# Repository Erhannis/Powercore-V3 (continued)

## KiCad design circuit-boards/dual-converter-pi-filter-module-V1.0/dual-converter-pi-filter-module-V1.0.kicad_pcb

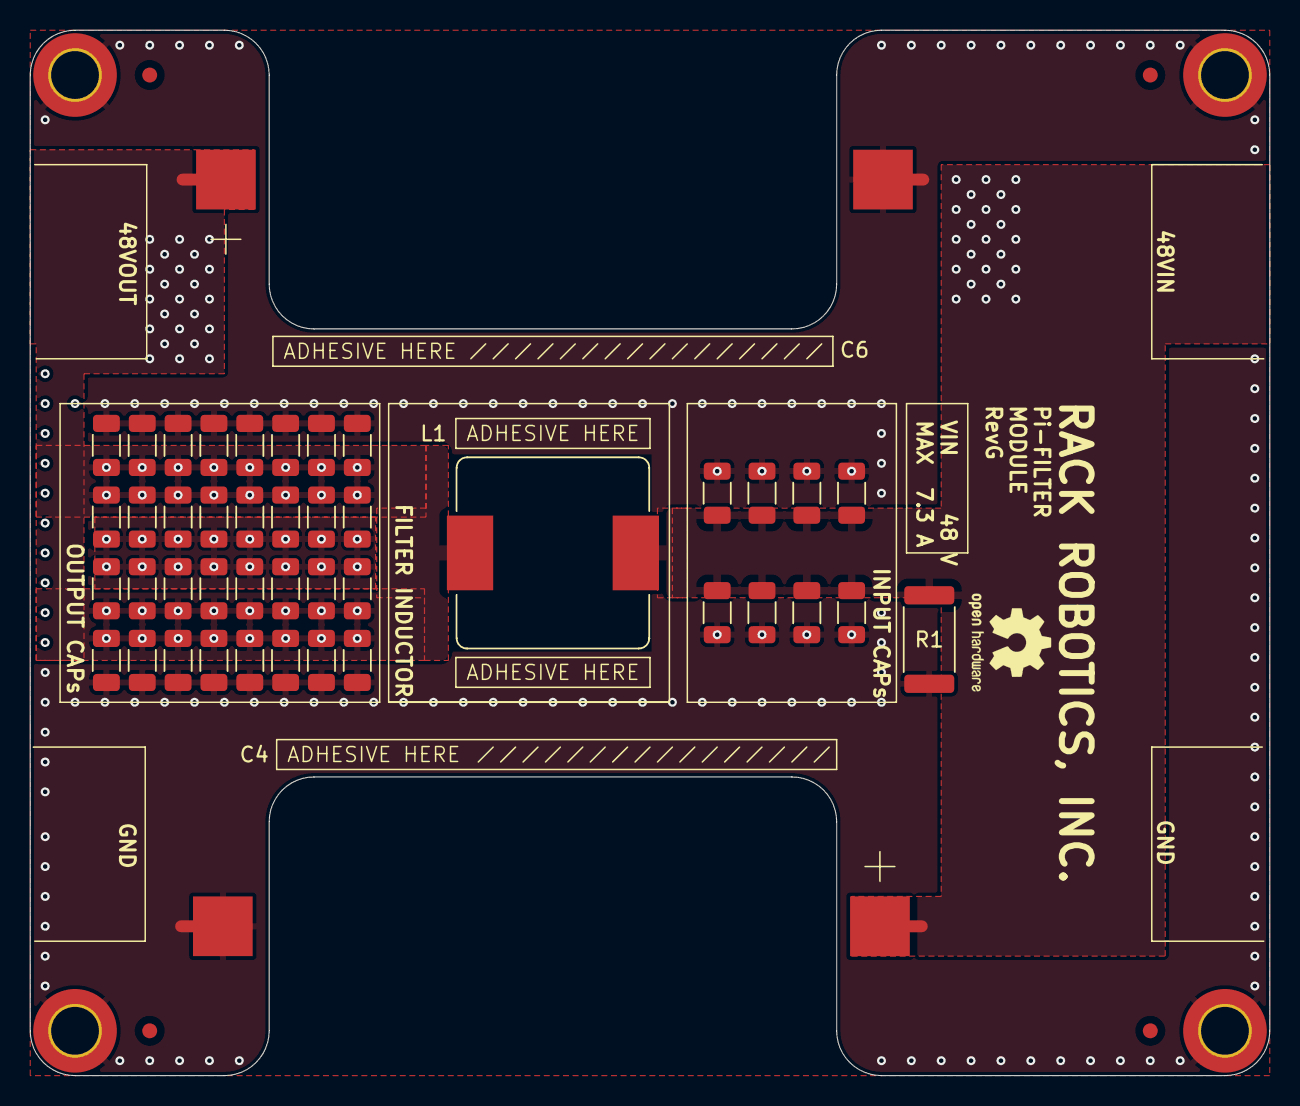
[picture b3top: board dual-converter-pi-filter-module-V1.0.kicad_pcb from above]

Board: 4 copper layers, 83.0 x 70.0 mm, 48 parts (0 on the bottom side), 3 nets.

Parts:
C1, C2, C3, C5, C7, C8, C9, C10, C11, C12, C13, C14, C15, C16, C17, C18, C19, C20, C21, C22, C23, C24, C25, C26, C27, C28, C29, C30, C31, C32, C33, C34, C35, C36, C37, C38, C39, C40, C41, C42: 10 uF; C_1206_3216Metric
C4, C6: 560 uF; PHA225
H1, H2, H3, H4: M3_DIN; MountingHole_3.2mm_M3_DIN965_Pad_TopBottom
L1: 18uH; SRP1245A
R1: 4.7K; R_2512_6332Metric

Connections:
+48V: C1.1, C2.1, C3.1, C4.1, C5.1, C7.1, C8.1, C9.1, C10.1, L1.1, R1.2
/FILTER_OUT: C6.1, C11.1, C12.1, C13.1, C14.1, C15.1, C16.1, C17.1, C18.1, C19.1, C20.1, C21.1, C22.1, C23.1, C24.1, C25.1, C26.1, C27.1, C28.1, C29.1, C30.1, C31.1, C32.1, C33.1, C34.1, C35.1, C36.1, C37.1, C38.1, C39.1, C40.1, C41.1, C42.1, L1.2
GND: C1.2, C2.2, C3.2, C4.2, C5.2, C6.2, C7.2, C8.2, C9.2, C10.2, C11.2, C12.2, C13.2, C14.2, C15.2, C16.2, C17.2, C18.2, C19.2, C20.2, C21.2, C22.2, C23.2, C24.2, C25.2, C26.2, C27.2, C28.2, C29.2, C30.2, C31.2, C32.2, C33.2, C34.2, C35.2, C36.2, C37.2, C38.2, C39.2, C40.2, C41.2, C42.2, H1.1, H2.1, H3.1, H4.1, R1.1

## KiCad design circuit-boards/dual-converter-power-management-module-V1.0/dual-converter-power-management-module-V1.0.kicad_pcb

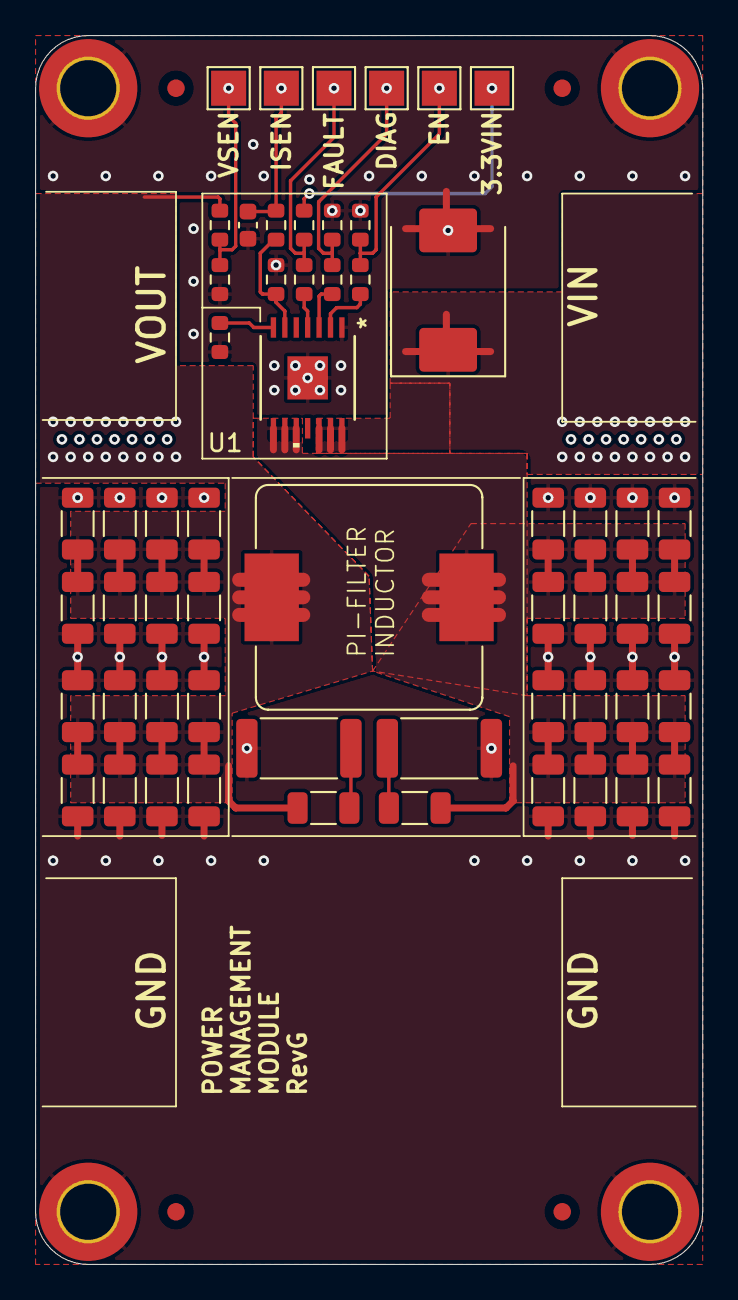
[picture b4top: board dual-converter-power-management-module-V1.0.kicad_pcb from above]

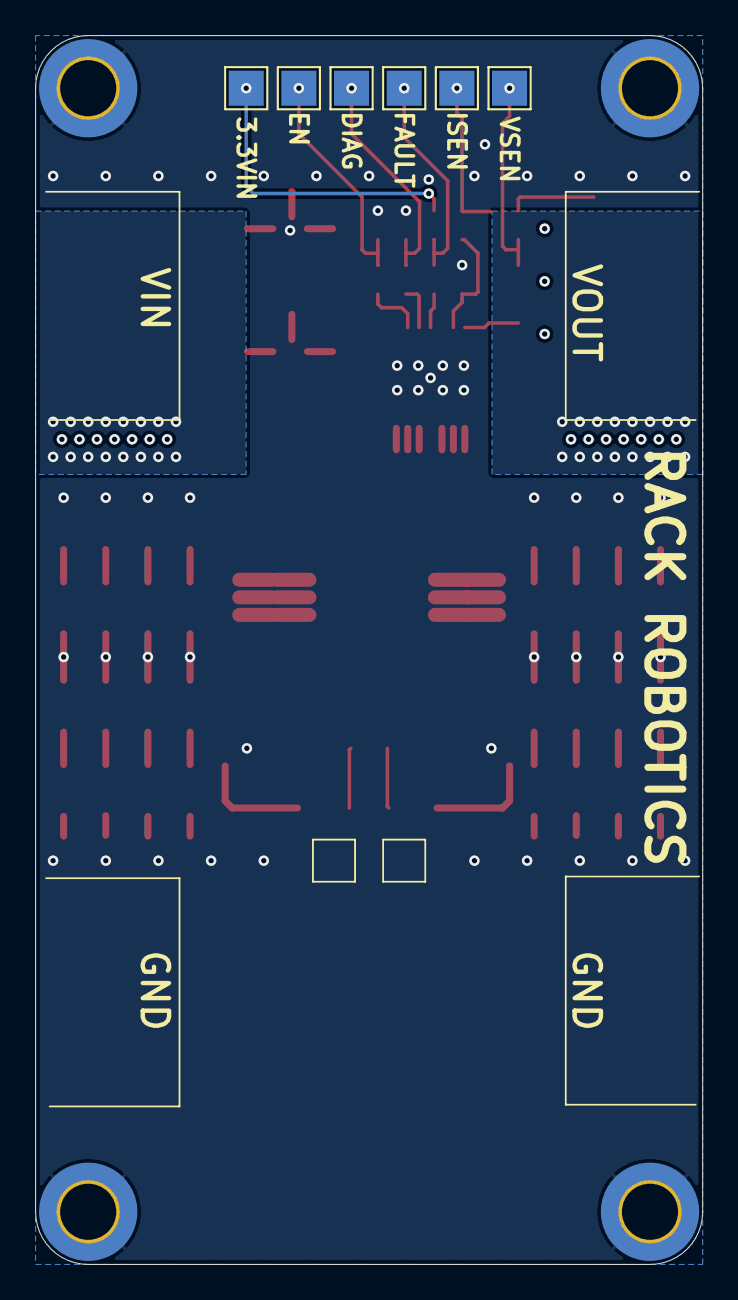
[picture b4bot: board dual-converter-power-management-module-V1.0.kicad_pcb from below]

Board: 4 copper layers, 38.0 x 70.0 mm, 67 parts (6 on the bottom side), 17 nets.

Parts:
C1: 1 uF; C_0603_1608Metric
C2, C3, C4, C5, C6, C7, C8, C9, C10, C11, C12, C13, C14, C15, C16, C17, C18, C19, C20, C21, C22, C23, C24, C25, C26, C27, C28, C29, C30, C31, C32, C33, C34, C35: 10 uF; C_1206_3216Metric
D1: SMCJ60A-E3/57T; D_SMC
H1, H2, H3, H4: M3_DIN; MountingHole_3.2mm_M3_DIN965_Pad_TopBottom
L1: 18uH; SRP1245A
R1, R6, R7: 100K; R_0603_1608Metric
R2, R3, R4, R5: 2.2K; R_0603_1608Metric
R8: 249R; R_0603_1608Metric
R9: 0R; R_0603_1608Metric
R10, R13: 1R; R_2512_6332Metric
R11: 172K; R_0603_1608Metric
R12: 10K; R_0603_1608Metric
TP1, TP2: 3.3VIN; TestPoint_Pad_2.0x2.0mm
TP3, TP4: ENABLE; TestPoint_Pad_2.0x2.0mm
TP5, TP6: DIAG_EN; TestPoint_Pad_2.0x2.0mm
TP7, TP10: FAULT; TestPoint_Pad_2.0x2.0mm
TP11, TP12: ISENSE; TestPoint_Pad_2.0x2.0mm
TP13, TP14: VSENSE_VIN; TestPoint_Pad_2.0x2.0mm
U1: TPS1HTC30AQPWPRQ1; TPS1HTC30-Q1

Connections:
+3.3V: R1.1, TP1.1, TP2.1
+48V: C19.1, C20.1, C21.1, C22.1, C23.1, C24.1, C25.1, C26.1, C27.1, C28.1, C29.1, C30.1, C31.1, C32.1, C33.1, C34.1, C35.1, L1.2, R11.1
+48VIN: D1.1 (A1), U1.12 (VS), U1.13 (VS), U1.14 (VS)
/FILTER_IN: C2.1, C3.1, C4.1, C5.1, C6.1, C7.1, C8.1, C9.1, C10.1, C11.1, C12.1, C13.1, C14.1, C15.1, C16.1, C17.1, C18.1, L1.1, U1.8 (VOUT), U1.9 (VOUT), U1.10 (VOUT)
/VSENSE_VIN: R11.2, R12.1, TP13.1, TP14.1
GND: C1.2, C2.2, C3.2, C4.2, C5.2, C6.2, C7.2, C8.2, C9.2, C11.2, C12.2, C13.2, C14.2, C15.2, C16.2, C17.2, C18.2, C19.2, C20.2, C21.2, C22.2, C23.2, C24.2, C25.2, C26.2, C28.2, C29.2, C30.2, C31.2, C32.2, C33.2, C34.2, C35.2, D1.2 (A2), H1.1, H2.1, H3.1, H4.1, R6.2, R7.2, R8.2, R9.2, R10.2, R12.2, R13.2, U1.1 (GND)
unnamed: C1.1, R5.1, TP11.1, TP12.1
unnamed: C10.2, R10.1
unnamed: C27.2, R13.1
unnamed: R1.2, R4.1, TP7.1, TP10.1
unnamed: R2.1, R6.1, TP3.1, TP4.1
unnamed: R3.1, R7.1, TP5.1, TP6.1
unnamed: R4.2, U1.4 (*FAULT)
unnamed: R3.2, U1.3 (DIAG_EN)
unnamed: R2.2, U1.2 (EN)
unnamed: R9.1, U1.7 (ILIM)
unnamed: R5.2, R8.1, U1.6 (SNS)
